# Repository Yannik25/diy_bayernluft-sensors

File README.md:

# diy_bayernluft-sensors

While our work to implement cheap DHT22 at: [diy_bayernluft](https://github.com/nielstron/diy_bayernluft), We also created a PCB with the SHT31 that Bayernluft ships with there products.

The gerber file was ordered on jlcpcb.com (best to order PCB with 1.2mm thickness)

The SHT31 was ordered at mouser: [SHT31-DIS-B2.5kS](https://www.mouser.de/ProductDetail/403-SHT31-DIS-B)

as well as the header pins with 2mm pitch: [Harwin M22-2580546](https://www.mouser.de/ProductDetail/Harwin/M22-2580546?qs=xxdqPuaJ%252Ba2PE%2FGuRM7plQ%3D%3D)

The schematic:

[Schematic](sch.png)

The designed and finished product can be seen here:

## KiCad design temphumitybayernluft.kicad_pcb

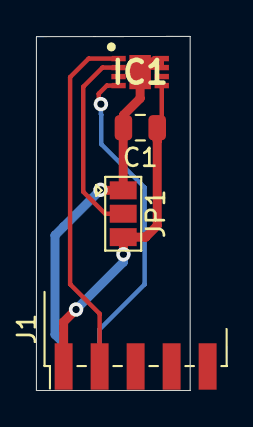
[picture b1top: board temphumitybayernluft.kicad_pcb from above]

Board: 2 copper layers, 8.5 x 19.7 mm, 4 parts (0 on the bottom side), 5 nets.

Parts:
C1: 100nF; C_0805_2012Metric
IC1: SHT31-DIS-B2.5KS; SON50P250X250X100-9N-D
J1: Conn_02x04_Odd_Even; PinHeader_2x05_P2.00mm_Vertical_SMD
JP1: SolderJumper_3_Bridged12; SolderJumper-3_P1.3mm_Open_Pad1.0x1.5mm

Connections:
+3V3: C1.1, IC1.5, J1.1, JP1.3
/SCL: IC1.4, J1.4
/SDA: IC1.1, J1.3
GND: C1.2, IC1.7, IC1.8, IC1.9, J1.2, JP1.1
unnamed: IC1.2, JP1.2

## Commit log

2021-01-09 Create Readme file
2021-01-09 add picture
2021-01-09 add design files
2022-01-28 Create LICENSE
